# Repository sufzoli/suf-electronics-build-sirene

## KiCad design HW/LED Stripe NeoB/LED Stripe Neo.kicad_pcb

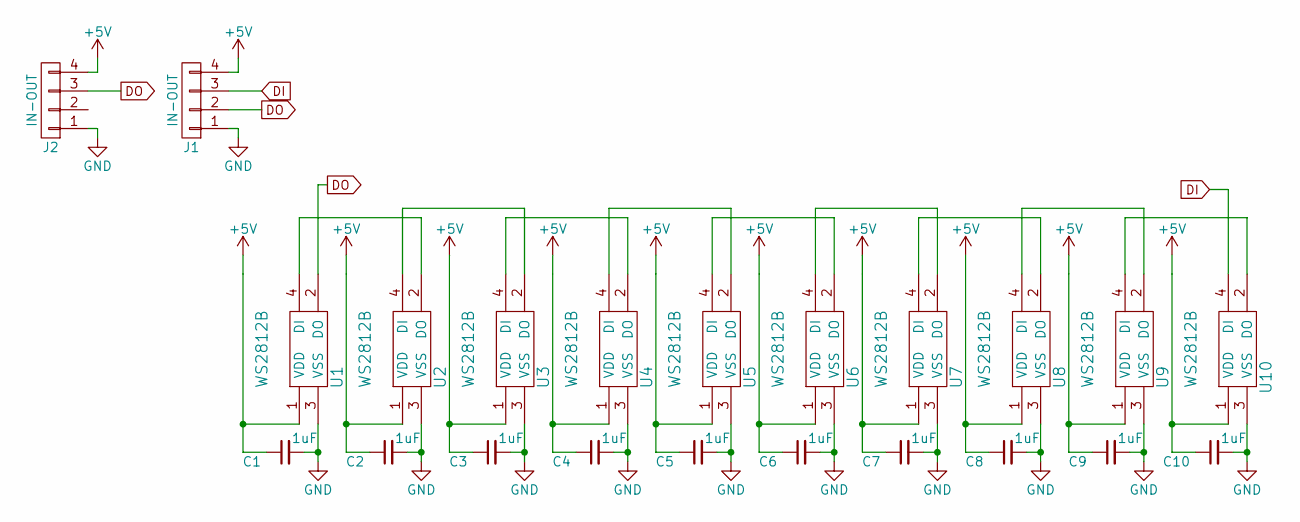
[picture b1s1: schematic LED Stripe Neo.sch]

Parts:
C1, C2, C3, C4, C5, C6, C7, C8, C9, C10: 1uF; C_0805_HandSoldering
J1, J2: IN-OUT; Pin_Header_Straight_1x04
U1, U2, U3, U4, U5, U6, U7, U8, U9, U10: WS2812B; LED-RGB_PLLC-6

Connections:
+5V: C1.1, C2.1, C3.1, C4.1, C5.1, C6.1, C7.1, C8.1, C9.1, C10.1, J1.4, J2.4, U1.1 (VDD), U2.1 (VDD), U3.1 (VDD), U4.1 (VDD), U5.1 (VDD), U6.1 (VDD), U7.1 (VDD), U8.1 (VDD), U9.1 (VDD), U10.1 (VDD)
DI: J1.3, U10.4 (DI)
DO: J1.2, J2.3, U1.2 (DO)
GND: C1.2, C2.2, C3.2, C4.2, C5.2, C6.2, C7.2, C8.2, C9.2, C10.2, J1.1, J2.1, U1.3 (VSS), U2.3 (VSS), U3.3 (VSS), U4.3 (VSS), U5.3 (VSS), U6.3 (VSS), U7.3 (VSS), U8.3 (VSS), U9.3 (VSS), U10.3 (VSS)
unnamed: U1.4 (DI), U2.2 (DO)
unnamed: U2.4 (DI), U3.2 (DO)
unnamed: U3.4 (DI), U4.2 (DO)
unnamed: U4.4 (DI), U5.2 (DO)
unnamed: U5.4 (DI), U6.2 (DO)
unnamed: U6.4 (DI), U7.2 (DO)
unnamed: U7.4 (DI), U8.2 (DO)
unnamed: U8.4 (DI), U9.2 (DO)
unnamed: U9.4 (DI), U10.2 (DO)

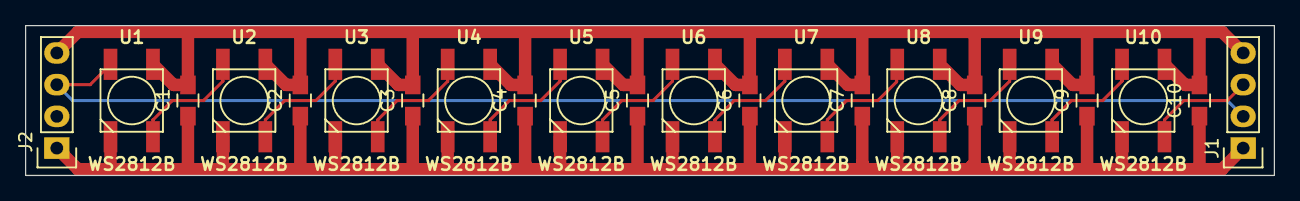
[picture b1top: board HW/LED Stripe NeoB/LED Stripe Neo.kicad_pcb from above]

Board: 2 copper layers, 100.0 x 12.0 mm, 22 parts (0 on the bottom side), 13 nets.

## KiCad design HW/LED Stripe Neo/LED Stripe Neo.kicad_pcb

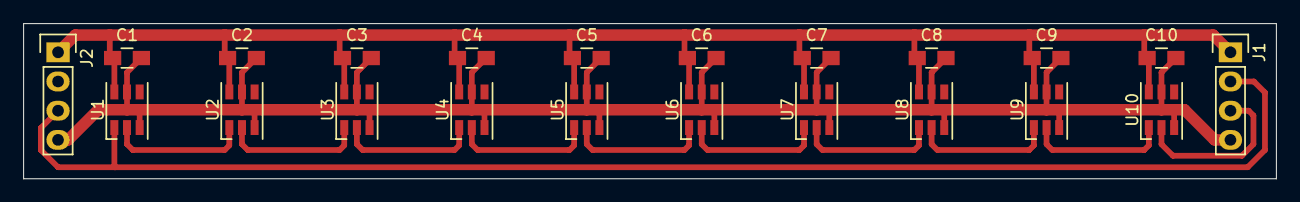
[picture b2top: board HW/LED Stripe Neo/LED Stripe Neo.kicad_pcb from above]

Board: 2 copper layers, 109.0 x 13.5 mm, 22 parts (0 on the bottom side), 13 nets.

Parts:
C1, C2, C3, C4, C5, C6, C7, C8, C9, C10: 1uF; C_0805_HandSoldering
J1, J2: IN-OUT; Pin_Header_Straight_1x04
U1, U2, U3, U4, U5, U6, U7, U8, U9, U10: WS2812; LED-RGB_PLLC-6

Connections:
+5V: C1.1, C2.1, C3.1, C4.1, C5.1, C6.1, C7.1, C8.1, C9.1, C10.1, J1.4, J2.4, U1.3, U1.5, U2.3, U2.5, U3.3, U3.5, U4.3, U4.5, U5.3, U5.5, U6.3, U6.5, U7.3, U7.5, U8.3, U8.5, U9.3, U9.5, U10.3, U10.5
DI: J1.3, U10.2
DO: J1.2, J2.3, U1.1
GND: C1.2, C2.2, C3.2, C4.2, C5.2, C6.2, C7.2, C8.2, C9.2, C10.2, J1.1, J2.1, U1.6, U2.6, U3.6, U4.6, U5.6, U6.6, U7.6, U8.6, U9.6, U10.6
unnamed: U1.2, U2.1
unnamed: U2.2, U3.1
unnamed: U3.2, U4.1
unnamed: U4.2, U5.1
unnamed: U5.2, U6.1
unnamed: U6.2, U7.1
unnamed: U7.2, U8.1
unnamed: U8.2, U9.1
unnamed: U9.2, U10.1

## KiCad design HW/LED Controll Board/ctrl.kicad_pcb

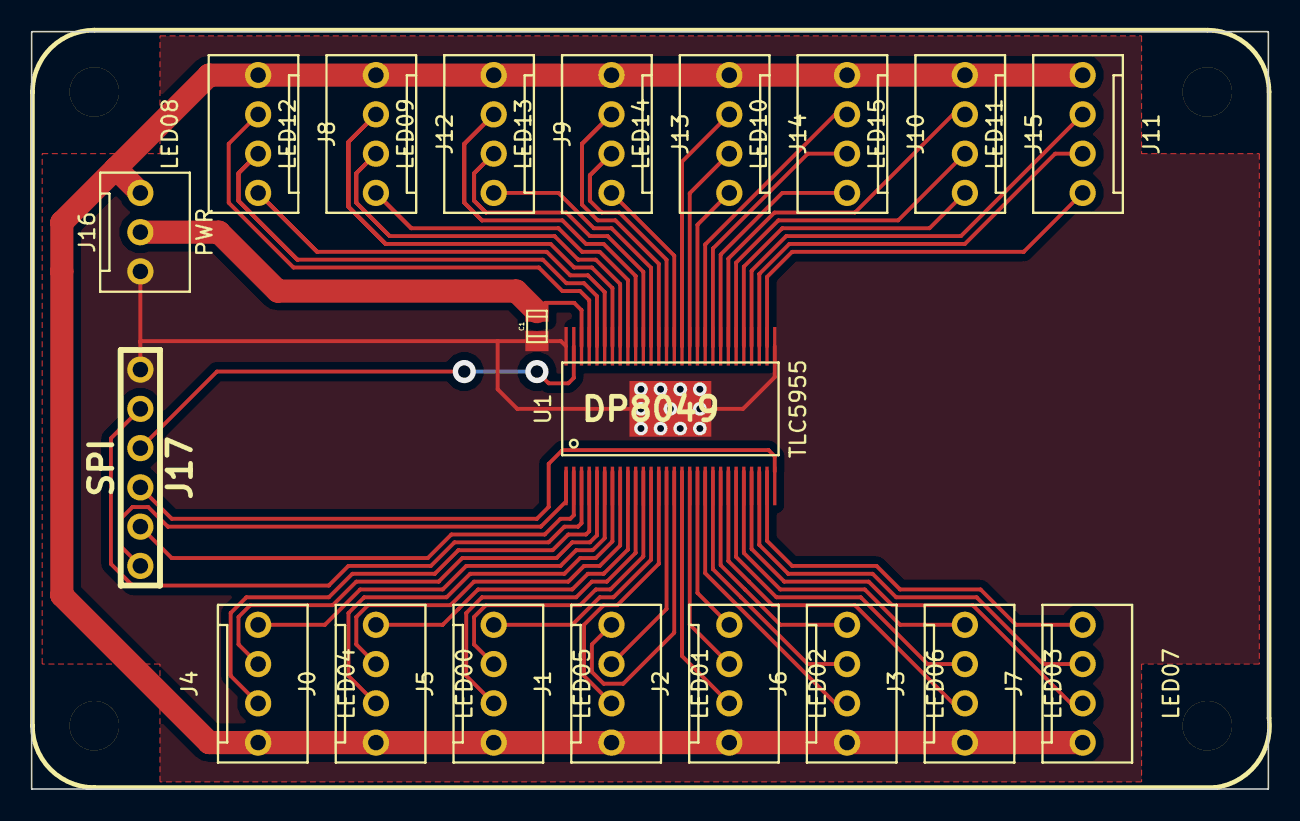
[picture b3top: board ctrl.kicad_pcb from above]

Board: 2 copper layers, 80.0 x 49.0 mm, 21 parts (0 on the bottom side), 56 nets.

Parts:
C1: 470nF/10V; c_0805
DP8049: DP8049
J0: LED00; CONN_NCW254-04S
J1: LED01; CONN_NCW254-04S
J2: LED02; CONN_NCW254-04S
J3: LED03; CONN_NCW254-04S
J4: LED04; CONN_NCW254-04S
J5: LED05; CONN_NCW254-04S
J6: LED06; CONN_NCW254-04S
J7: LED07; CONN_NCW254-04S
J8: LED08; CONN_NCW254-04S
J9: LED09; CONN_NCW254-04S
J10: LED10; CONN_NCW254-04S
J11: LED11; CONN_NCW254-04S
J12: LED12; CONN_NCW254-04S
J13: LED13; CONN_NCW254-04S
J14: LED14; CONN_NCW254-04S
J15: LED15; CONN_NCW254-04S
J16: PWR; CONN_NCW254-03S
J17: SPI; HDR-6
U1: TLC5955; HTSSOP-56

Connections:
GND: C1.2, J16.1, J17.1, U1.29, U1.56, U1.TP
unnamed: J4.3, U1.5
unnamed: J0.2, U1.7
unnamed: J0.3, U1.8
unnamed: J0.4, U1.9
unnamed: J1.2, U1.13
unnamed: J1.3, U1.14
unnamed: J1.4, U1.15
unnamed: J2.2, U1.16
unnamed: J2.3, U1.17
unnamed: J2.4, U1.18
unnamed: J3.2, U1.22
unnamed: J3.3, U1.23
unnamed: J3.4, U1.24
unnamed: J4.2, U1.4
unnamed: J4.4, U1.6
unnamed: J5.2, U1.10
unnamed: J5.3, U1.11
unnamed: J5.4, U1.12
unnamed: J6.2, U1.19
unnamed: J6.3, U1.20
unnamed: J6.4, U1.21
unnamed: J7.2, U1.25
unnamed: J7.3, U1.26
unnamed: J7.4, U1.27
unnamed: J8.2, U1.53
unnamed: J8.3, U1.52
unnamed: J8.4, U1.51
unnamed: J9.2, U1.47
unnamed: J9.3, U1.46
unnamed: J0.1, J1.1, J2.1, J3.1, J4.1, J5.1, J6.1, J7.1, J8.1, J9.1, J10.1, J11.1, J12.1, J13.1, J14.1, J15.1, J16.3
unnamed: J17.2, U1.3
unnamed: J17.3, U1.55
unnamed: J17.4, U1.28
unnamed: J17.5, U1.2
unnamed: J17.6, U1.1
unnamed: J14.3, U1.40
unnamed: J9.4, U1.45
unnamed: J10.2, U1.38
unnamed: J10.3, U1.37
unnamed: J10.4, U1.36
unnamed: J11.2, U1.32
unnamed: J11.3, U1.31
unnamed: J11.4, U1.30
unnamed: J12.2, U1.50
unnamed: J12.3, U1.49
unnamed: J12.4, U1.48
unnamed: J13.2, U1.44
unnamed: J13.3, U1.43
unnamed: J13.4, U1.42
unnamed: J14.2, U1.41
unnamed: J14.4, U1.39
unnamed: J15.2, U1.35
unnamed: J15.3, U1.34
unnamed: J15.4, U1.33
unnamed: C1.1, J16.2, U1.54

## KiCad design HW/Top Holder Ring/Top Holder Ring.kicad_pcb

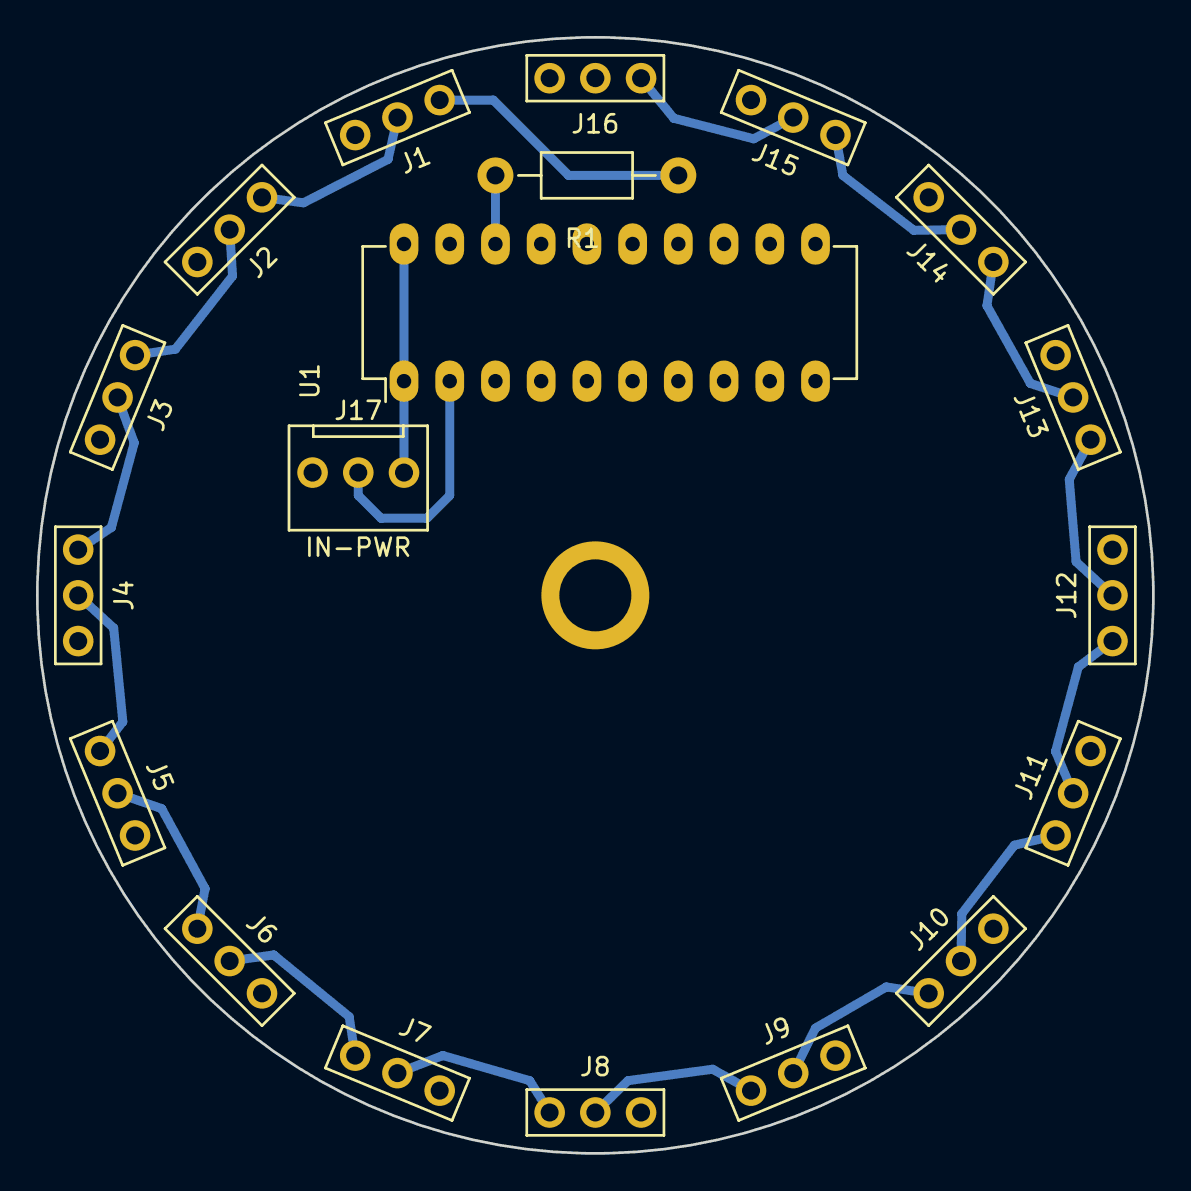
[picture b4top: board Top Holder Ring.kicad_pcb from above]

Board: 2 copper layers, 62.0 x 62.0 mm, 20 parts (0 on the bottom side), 20 nets.

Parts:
J1, J2, J3, J4, J5, J6, J7, J8, J9, J10, J11, J12, J13, J14, J15, J16: CONN_01X03; hdr_straight_1x3
J17: IN-PWR; CONN_NCW254-03S
MNT_HOLE_4: Val**; MNT_HOLE_4
R1: 470; Resistor_Horizontal_RM10mm
U1: 74HC2T45; DIP-20_W7.62mm_LongPads

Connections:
GND: J1.1, J2.1, J3.1, J4.1, J5.1, J6.1, J7.1, J8.1, J9.1, J10.1, J11.1, J12.1, J13.1, J14.1, J15.1, J16.1, J17.1, U1.10, U1.19
unnamed: J1.2, J2.3
unnamed: J1.3, R1.1
unnamed: J2.2, J3.3
unnamed: J3.2, J4.3
unnamed: J4.2, J5.3
unnamed: J5.2, J6.3
unnamed: J6.2, J7.3
unnamed: J7.2, J8.3
unnamed: J8.2, J9.3
unnamed: J10.2, J11.3
unnamed: J9.2, J10.3
unnamed: J11.2, J12.3
unnamed: J12.2, J13.3
unnamed: J13.2, J14.3
unnamed: J14.2, J15.3
unnamed: J15.2, J16.3
unnamed: J17.2, U1.2
unnamed: R1.2, U1.18
VCC: J17.3, U1.1, U1.20

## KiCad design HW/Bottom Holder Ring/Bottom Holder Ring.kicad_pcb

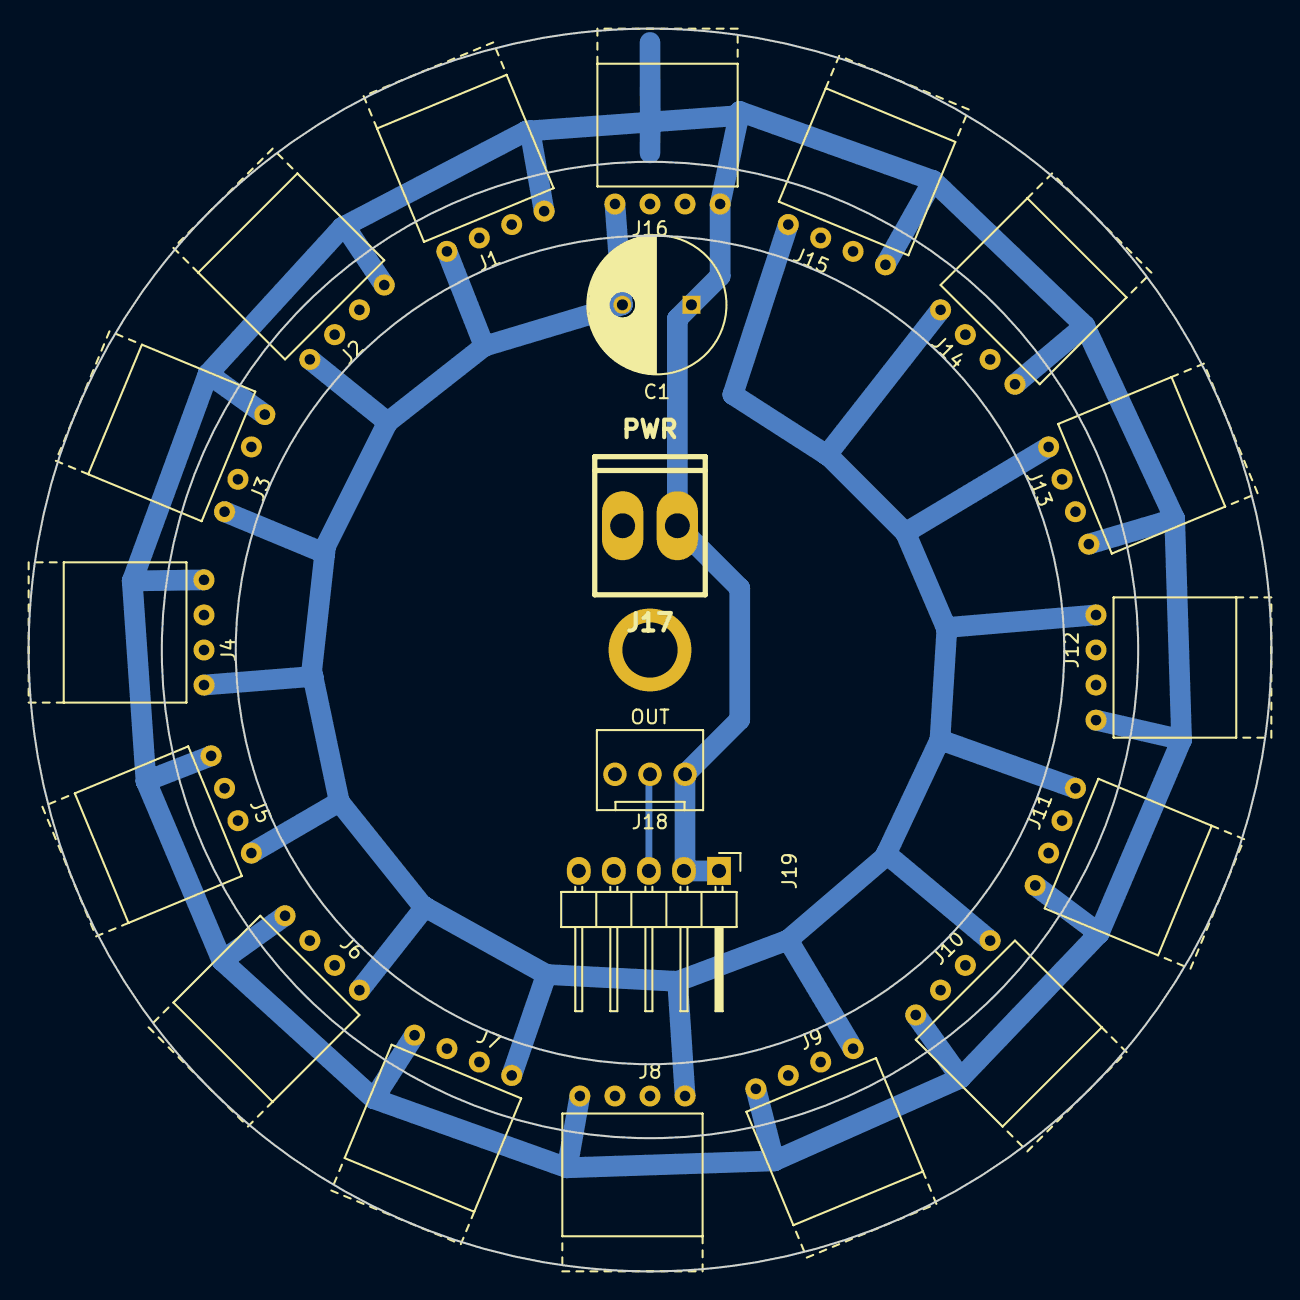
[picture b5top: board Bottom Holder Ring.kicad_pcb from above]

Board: 2 copper layers, 90.0 x 90.0 mm, 21 parts (0 on the bottom side), 3 nets.

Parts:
C1: 1000uF/10V; C_Radial_D10_L13_P5
J1, J2, J3, J4, J5, J6, J7, J8, J9, J10, J11, J12, J13, J14, J15, J16: CONN_01X04; hdr_f_01x4
J17: PWR; CONN_NCW396-02S
J18: OUT; CONN_NCW254-03S
J19: RPI; Pin_Header_Angled_1x05
MNT_HOLE_4: Val**; MNT_HOLE_4

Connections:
GND: C1.2, J1.1, J2.1, J3.1, J4.1, J5.1, J6.1, J7.1, J8.1, J9.1, J10.1, J11.1, J12.1, J13.1, J14.1, J15.1, J16.1, J17.2, J18.3, J19.4, J19.5
unnamed: J18.2, J19.3
VCC: C1.1, J1.4, J2.4, J3.4, J4.4, J5.4, J6.4, J7.4, J8.4, J9.4, J10.4, J11.4, J12.4, J13.4, J14.4, J15.4, J16.4, J17.1, J18.1, J19.1, J19.2

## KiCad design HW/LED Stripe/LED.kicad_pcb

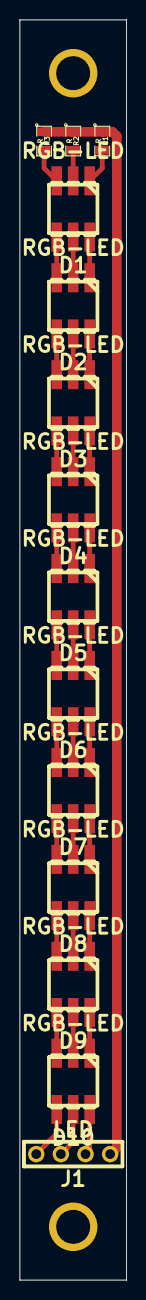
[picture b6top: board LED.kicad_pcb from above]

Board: 2 copper layers, 11.0 x 130.0 mm, 16 parts (0 on the bottom side), 34 nets.

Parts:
D1, D2, D3, D4, D5, D6, D7, D8, D9, D10: RGB-LED; PLCC-6
J1: LED; HDR-4
MNT_HOLE_3.5S, MNT_HOLE_3.5S#2: Val**; MNT_HOLE_3.5S
R1, R2, R3: R; SM0805

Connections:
unnamed: D2.5, D3.2
unnamed: D2.6, D3.1
unnamed: D1.4, D2.3
unnamed: D1.5, D2.2
unnamed: D1.6, D2.1
unnamed: D1.3, R3.2
unnamed: D1.2, R2.2
unnamed: D1.1, R1.2
unnamed: J1.1, R1.1, R2.1, R3.1
unnamed: D2.4, D3.3
unnamed: D10.5, J1.3
unnamed: D10.6, J1.2
unnamed: D10.4, J1.4
unnamed: D9.4, D10.3
unnamed: D9.6, D10.1
unnamed: D9.5, D10.2
unnamed: D7.5, D8.2
unnamed: D8.4, D9.3
unnamed: D8.5, D9.2
unnamed: D8.6, D9.1
unnamed: D7.4, D8.3
unnamed: D7.6, D8.1
unnamed: D6.4, D7.3
unnamed: D6.5, D7.2
unnamed: D6.6, D7.1
unnamed: D5.4, D6.3
unnamed: D5.5, D6.2
unnamed: D5.6, D6.1
unnamed: D4.4, D5.3
unnamed: D4.5, D5.2
unnamed: D4.6, D5.1
unnamed: D3.4, D4.3
unnamed: D3.5, D4.2
unnamed: D3.6, D4.1

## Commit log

2015-06-25 Siren 3D Model added
2015-06-25 W22812 Based design added
2015-06-26 Fix WS2812 vs WS2812B footprint differences
2015-06-26 WS2812B version added (transfer only)
2015-06-26 WS2812B SCH/PCB added
2015-12-12 Changed to Raspberry PI2
2016-01-13 Holder (level shifter) PCBs added, python code modified
2021-03-20 Add VS1053 related things
